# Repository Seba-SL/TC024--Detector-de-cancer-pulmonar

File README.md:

# TC024--Detector-de-cancer-pulmonar

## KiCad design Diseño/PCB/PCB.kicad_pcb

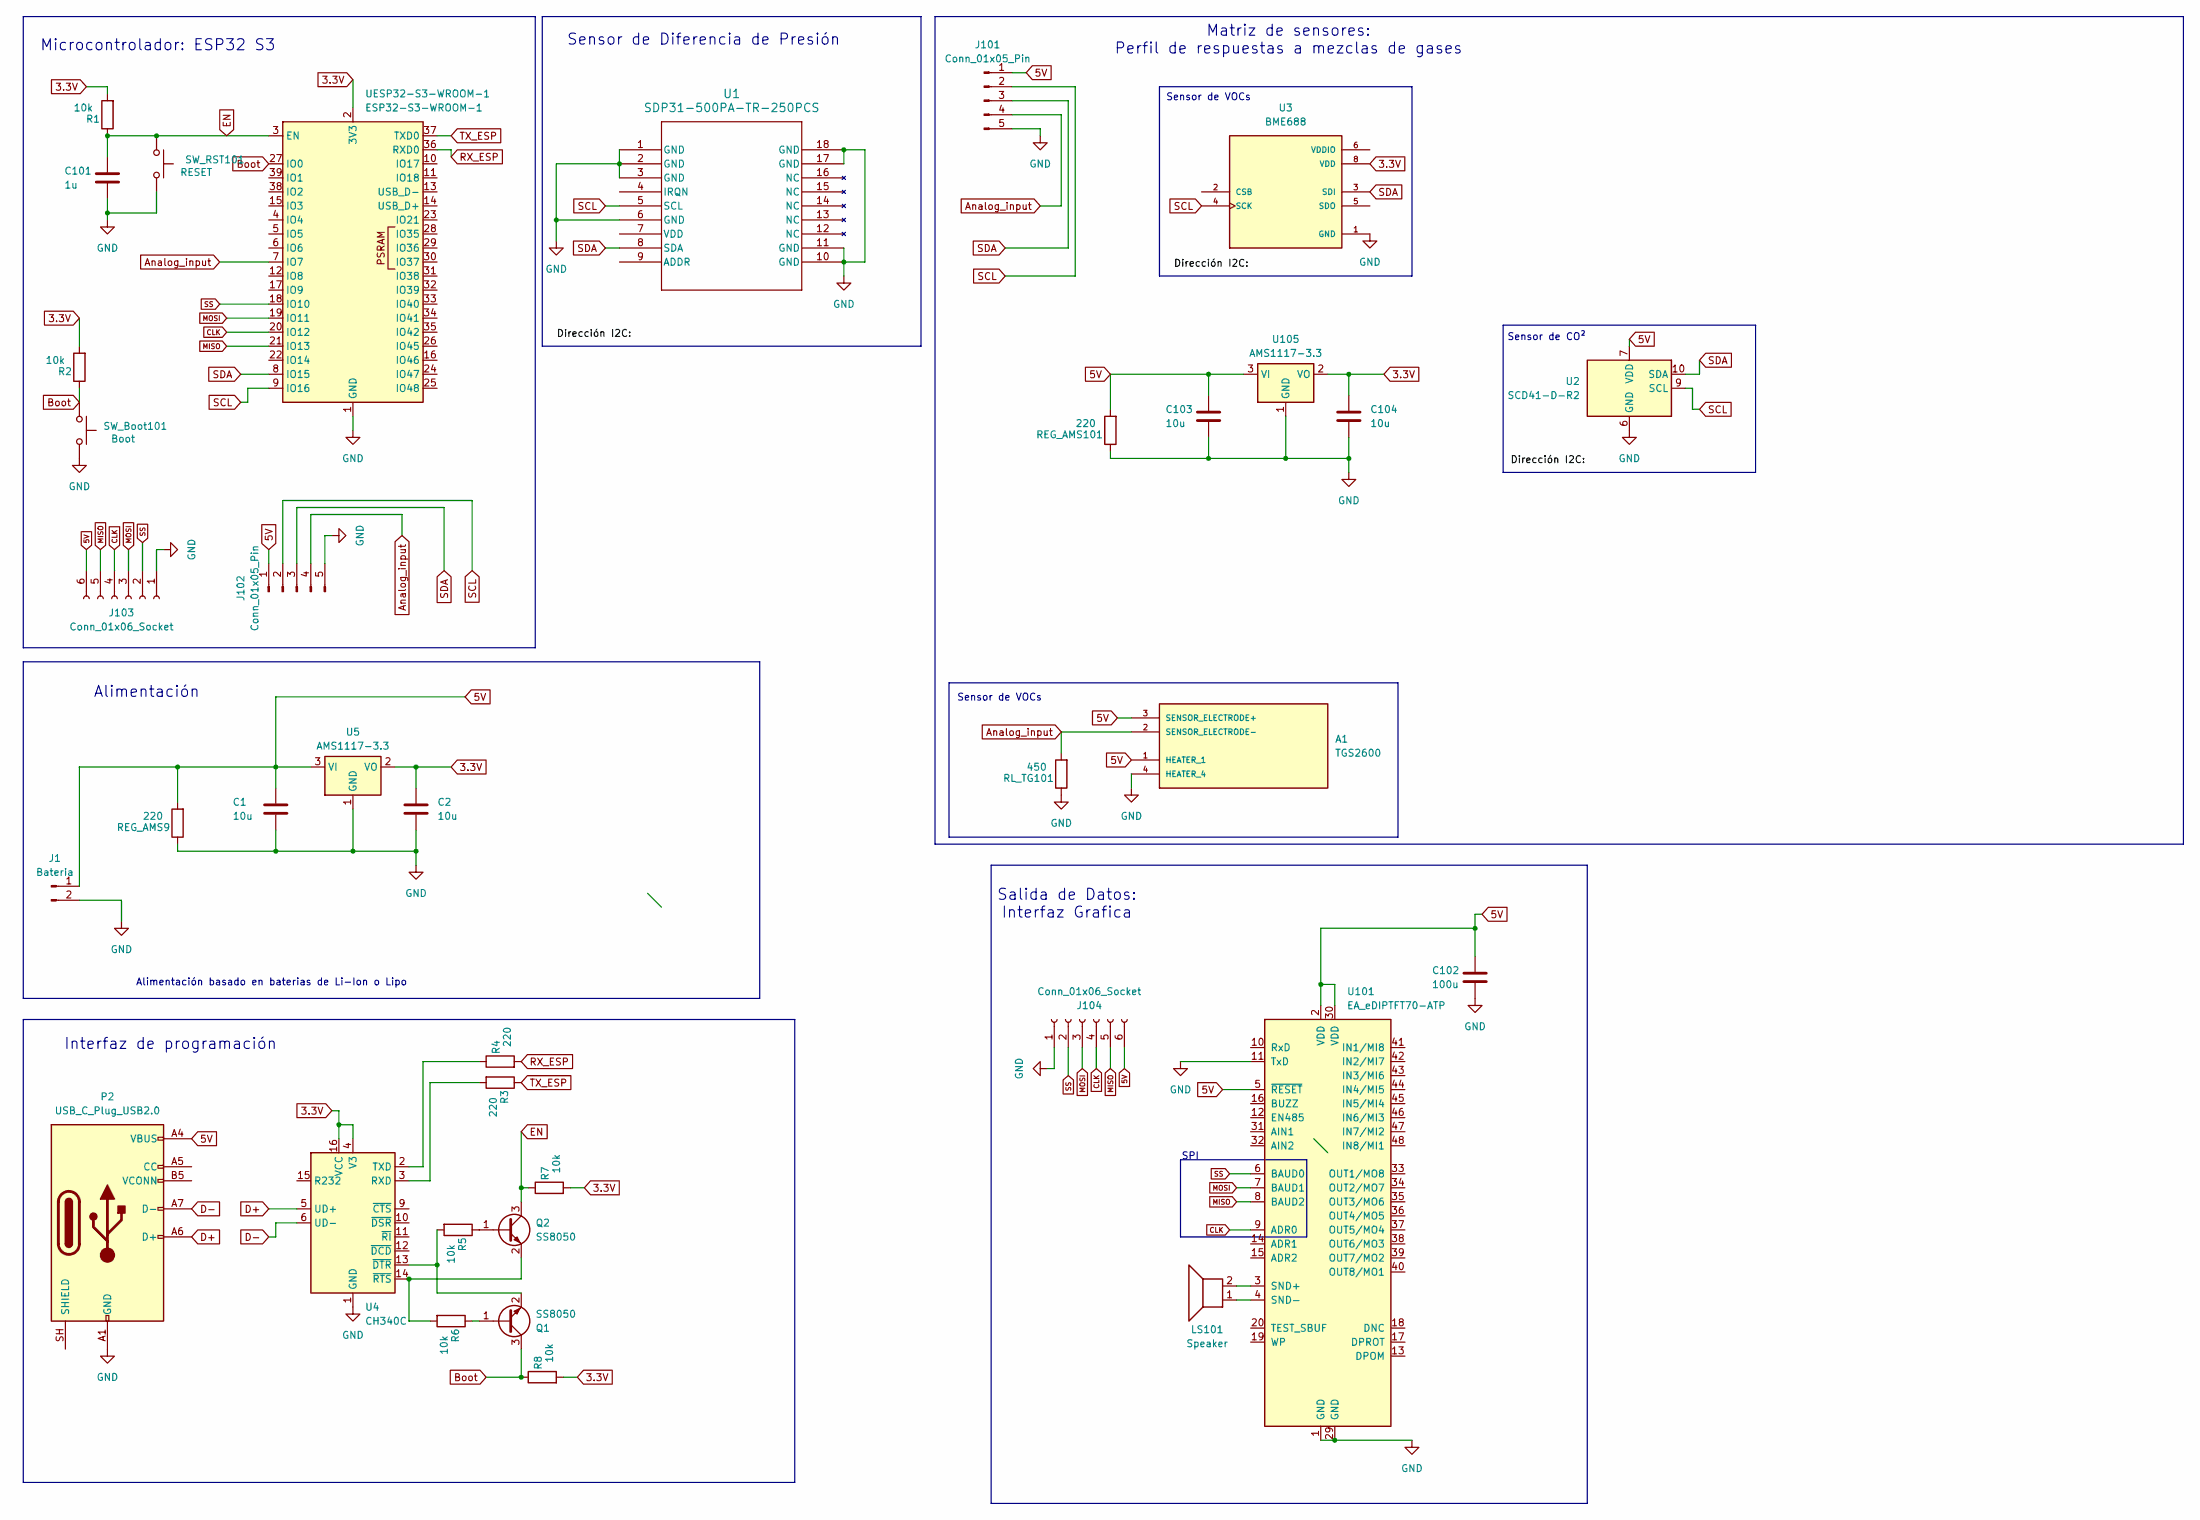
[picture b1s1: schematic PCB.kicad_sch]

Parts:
A1: TGS2600; TO255P920H830-4; PARTREV 03/22
C1, C2, C103, C104: 10u; C_1808_4520Metric_Pad1.72x2.30mm_HandSolder
C101: 1u; C_1808_4520Metric_Pad1.72x2.30mm_HandSolder
C102: 100u; C_1808_4520Metric_Pad1.72x2.30mm_HandSolder
J1: Bateria; PinHeader_1x02_P2.54mm_Vertical
J101, J102: Conn_01x05_Pin; PinSocket_1x05_P2.54mm_Vertical
J103, J104: Conn_01x06_Socket; PinSocket_1x06_P2.54mm_Vertical
LS101: Speaker; PinHeader_1x02_P2.54mm_Vertical
P2: USB_C_Plug_USB2.0; USB_C_Receptacle_GCT_USB4110
Q1, Q2: SS8050; SOT-23
R1, R2, R5, R6, R7, R8: 10k; R_0201_0603Metric_Pad0.64x0.40mm_HandSolder
R3, R4: 220; R_0201_0603Metric_Pad0.64x0.40mm_HandSolder
REG_AMS9, REG_AMS101: 220; R_0201_0603Metric_Pad0.64x0.40mm_HandSolder
RL_TG101: 450; R_0201_0603Metric_Pad0.64x0.40mm_HandSolder
SW_Boot101: Boot; SW_Push_SPST_NO_Alps_SKRK
SW_RST101: RESET; SW_Push_SPST_NO_Alps_SKRK
U1: SDP31-500PA-TR-250PCS; SDP31-500PA-TR-250PCS_SEN
U2: SCD41-D-R2; Sensirion_SCD4x-1EP_10.1x10.1mm_P1.25mm_EP4.8x4.8mm
U3: BME688; IC_BME688; PARTREV 1.0
U4: CH340C; SOIC-16_3.9x9.9mm_P1.27mm
U5, U105: AMS1117-3.3; SOT-223-3_TabPin2
U101: EA_eDIPTFT70-ATP; EA_eDIPTFT70-XXX
UESP32-S3-WROOM-1: ESP32-S3-WROOM-1

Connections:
3.3V: C2.1, C104.1, R1.2, R2.2, R7.2, R8.2, U3.8 (VDD), U4.4 (V3), U4.16 (VCC), U5.2 (VO), U105.2 (VO), UESP32-S3-WROOM-1.2 (3V3); also elsewhere on the board
5V: A1.1 (HEATER_1), A1.3 (SENSOR_ELECTRODE+), C1.1, C102.1, C103.1, J1.1, J101.1, J102.1, J103.6, J104.6, P2.A4 (VBUS), P2.A9 (VBUS), P2.B4 (VBUS), P2.B9 (VBUS), REG_AMS9.2, REG_AMS101.2, U2.7 (VDD), U2.19 (VDD), U5.3 (VI), U101.2 (VDD), U101.5 (~RESET), U101.30 (VDD), U105.3 (VI); also elsewhere on the board
Analog_input: A1.2 (SENSOR_ELECTRODE-), J101.4, J102.4, RL_TG101.2, UESP32-S3-WROOM-1.7 (IO7)
Boot: Q1.3 (C), R2.1, R8.1, SW_Boot101.2, UESP32-S3-WROOM-1.27 (IO0)
CLK: J103.4, J104.4, U101.9 (ADR0), UESP32-S3-WROOM-1.20 (IO12)
D+: P2.A6 (D+), U4.5 (UD+)
D-: P2.A7 (D-), U4.6 (UD-)
EN: C101.1, Q2.3 (C), R1.1, R7.1, SW_RST101.2, UESP32-S3-WROOM-1.3 (EN)
GND: A1.4 (HEATER_4), C1.2, C2.2, C101.2, C102.2, C103.2, C104.2, J1.2, J101.5, J102.5, J103.1, J104.1, P2.A1 (GND), P2.A12 (GND), P2.B1 (GND), P2.B12 (GND), REG_AMS9.1, REG_AMS101.1, RL_TG101.1, SW_Boot101.1, SW_RST101.1, U1.1 (GND), U1.2 (GND), U1.3 (GND), U1.6 (GND), U1.10 (GND), U1.11 (GND), U1.17 (GND), U1.18 (GND), U2.6 (GND), U2.20 (GND), U2.21 (GND), U3.1 (GND), U3.7 (GND), U4.1 (GND), U5.1 (GND), U101.1 (GND), U101.11 (TxD), U101.29 (GND), U105.1 (GND), UESP32-S3-WROOM-1.1 (GND), UESP32-S3-WROOM-1.40 (GND), UESP32-S3-WROOM-1.41 (GND); also elsewhere on the board
MISO: J103.5, J104.5, U101.8 (BAUD2), UESP32-S3-WROOM-1.21 (IO13)
MOSI: J103.3, J104.3, U101.7 (BAUD1), UESP32-S3-WROOM-1.19 (IO11)
unnamed: Q1.1 (B), R6.1
unnamed: Q1.2 (E), R5.2, U4.13 (~DTR)
unnamed: Q2.1 (B), R5.1
unnamed: Q2.2 (E), R6.2, U4.14 (~RTS)
unnamed: R3.2, U4.3 (RXD)
unnamed: R4.1, U4.2 (TXD)
unnamed: LS101.2, U101.3 (SND+)
unnamed: LS101.1, U101.4 (SND-)
RX_ESP: R4.2, UESP32-S3-WROOM-1.36 (RXD0)
SCL: J101.2, J102.2, U1.5 (SCL), U2.9 (SCL), U3.4 (SCK), UESP32-S3-WROOM-1.9 (IO16); also elsewhere on the board
SDA: J101.3, J102.3, U1.8 (SDA), U2.10 (SDA), U3.3 (SDI), UESP32-S3-WROOM-1.8 (IO15); also elsewhere on the board
SS: J103.2, J104.2, U101.6 (BAUD0), UESP32-S3-WROOM-1.18 (IO10)
TX_ESP: R3.1, UESP32-S3-WROOM-1.37 (TXD0)

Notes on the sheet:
Sensor de Diferencia de Presión
Alimentación
SPI
Sensor de VOCs
Matriz de sensores: Perfil de respuestas a mezclas de gases
Sensor de CO²
Salida de Datos: Interfaz Grafica
Microcontrolador: ESP32 S3
Alimentación basado en baterias de Li-Ion o Lipo
Interfaz de programación

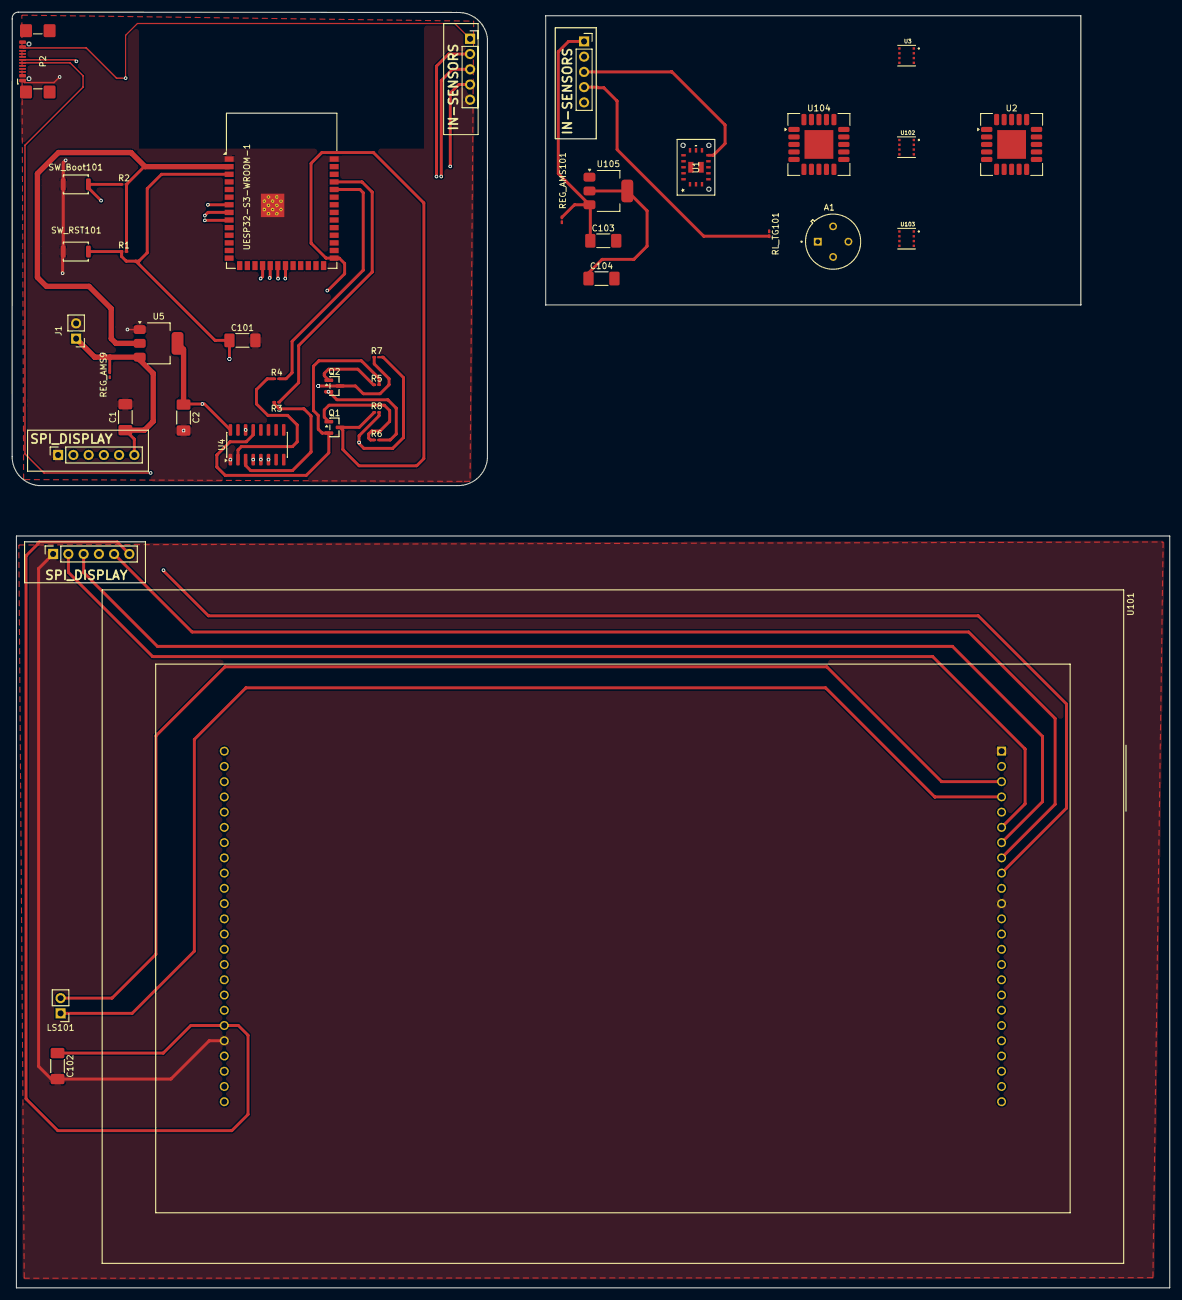
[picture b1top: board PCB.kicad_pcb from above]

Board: 6 copper layers, 192.9 x 212.6 mm, 40 parts (0 on the bottom side), 24 nets.

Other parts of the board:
U102, U103: BME688; IC_BME688
U104: SCD41-D-R2; Sensirion_SCD4x-1EP_10.1x10.1mm_P1.25mm_EP4.8x4.8mm

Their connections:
3.3V: U102.8 (VDD), U103.8 (VDD); also elsewhere on the board
5V: U104.7 (VDD), U104.19 (VDD); also elsewhere on the board
GND: U102.1 (GND), U102.7 (GND), U103.1 (GND), U103.7 (GND), U104.6 (GND), U104.20 (GND), U104.21 (GND); also elsewhere on the board
SCL: U102.4 (SCK), U103.4 (SCK), U104.9 (SCL); also elsewhere on the board
SDA: U102.3 (SDI), U103.3 (SDI), U104.10 (SDA); also elsewhere on the board
